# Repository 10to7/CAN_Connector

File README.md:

CAN_Connector
=============

**Warning** _currently untested, may contain errors._

A basic strip of connectors for a can bus.

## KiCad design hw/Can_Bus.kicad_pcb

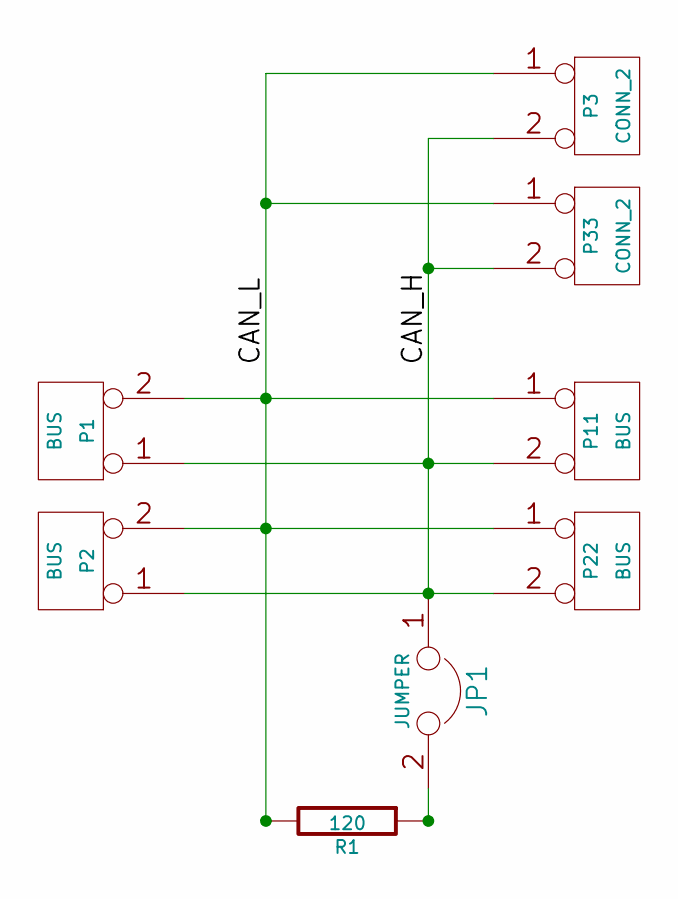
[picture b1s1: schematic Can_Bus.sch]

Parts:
JP1: JUMPER
P1, P2, P11, P22: BUS
P3, P33: CONN_2
R1: 120

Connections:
/CAN_H: JP1.1, P1.1, P2.1, P3.2 (PM), P11.2 (PM), P22.2 (PM), P33.2 (PM)
/CAN_L: P1.2 (PM), P2.2 (PM), P3.1, P11.1, P22.1, P33.1, R1.2
unnamed: JP1.2, R1.1

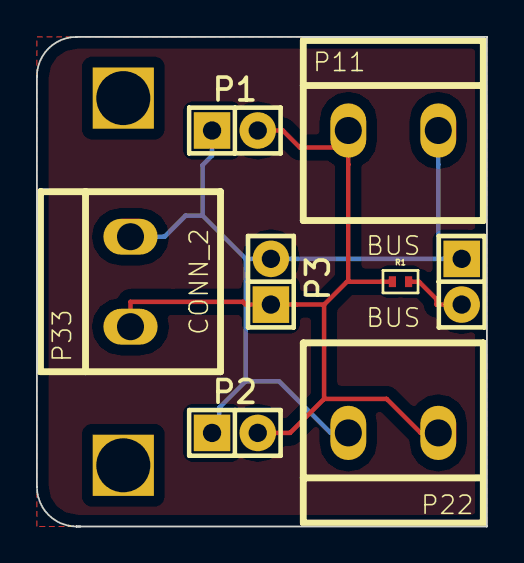
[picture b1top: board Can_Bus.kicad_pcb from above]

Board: 2 copper layers, 25.0 x 27.2 mm, 10 parts (0 on the bottom side), 3 nets.

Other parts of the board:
3mmHole, 3mmHole_1: VAL**; 3mmHole

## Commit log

2014-07-06 Added a simple can bus interconnecting node
2014-07-09 Added redering of the boards
